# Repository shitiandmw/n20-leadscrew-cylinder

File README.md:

# n20-leadscrew-cylinder

**A 3D-printable linear actuator for a model excavator that looks like a hydraulic cylinder.** It is driven by a standard N20 gearmotor with an integrated M3 leadscrew, used exactly as bought.

The [Sand / Lab application](excavator_app/README.md) turns the existing ARM60 / Track R4 model into a Docker-deployable digging sandbox. A desktop displays the complete CAD assembly and a live sand pit: a deformable sand bed that slumps to its angle of repose, plus free grains wherever sand is cut, carried or poured; a phone pairs by QR code and controls the boom, stick, bucket, slew and tracks over WebSocket. It includes touch joysticks, keyboard controls, emergency stop, connection watchdogs, and verified scoop-and-pour physics. Run `docker compose up --build -d` from `excavator_app/` to start it.

The [complete tracked arm60 excavator](excavator_60mm/README.md) adds independent track drives, steel-pinned links, sprung idlers, bearing-supported geared slewing and a recessed slew cover around the existing 60 mm arm. Its R3 upper body follows the Cat 320 layout: cab front-left, tank housing and stepped toolbox front-right, an engine hood with a battery hatch, and a curved counterweight on the 189 mm tail-swing radius holding steel ballast. Two 18650 cells sit in a cradle sized from manufacturer datasheets. Track R4 adds Berco-referenced sprockets engaging steel bushings, rollers with two outer guide flanges, and a 394 mm track stance around the 308 mm upper platform. Offline playback shows the loaded contact simulation, including passive wheel rotation, idler take-up, forward/reverse travel and braking. The preview allows independent boom and slew travel; track clearance is managed by the operator. Its folder includes parametric CAD, printable parts, a complete STEP assembly, an offline preview, mechanical assembly instructions and reproducible geometry, load and physics simulations. Physical fit, powered operation and payload still require prototype testing.

The [R10 arm with two boom actuators and a deeper boomerang profile](excavator_arm_dual/README.md) implements the user's latest revision: symmetric boom drives at Y = ±50 mm and a hollow, tapered boom with a 76.7 mm middle section, retaining the original joint coordinates and five replaceable teeth. All four actuators are modeled independently. Fixed-base rigid-body simulations track both unloaded and 150 g cycles under an assumed 100 N limit per drive; each boom drive peaks at 58.4 N with the example load. CAD, printable parts, assembly instructions, an offline viewer and a 54-second motion video are included. A feedback-offset case demonstrates unequal load sharing; hardware synchronization, structural strength and soil interaction remain unverified.

R6–R9 and their motion-review files have been removed from the workspace at the user's request. The current arm is R10 in `excavator_arm_dual/`, with actuator dependencies in `actuator_v6/`. Earlier tracked designs remain in Git history. The complete vehicle and sandbox still use the earlier ARM60 model; R10 has not been integrated into them.

The new [ground-mounted excavator arm](excavator_arm/README.md) follows Cat 320 proportions at 1:12, with a 475 mm bent box boom, 241.7 mm stick and inward-facing bucket. Four V6 actuators use 100/120/75 mm leadscrews with regenerated matching parts and end-stop boards. It includes an [offline motion preview](excavator_arm/3D_preview.html), [STEP assembly](excavator_arm/step/excavator_arm_assembly.step), STL meshes, manufacturer references, dimensioned drawings and geometric validation. There is no vehicle chassis.

A separate [60 mm stroke edition](excavator_arm_60mm/README.md) uses four identical actuators and smaller 1:15 proportions: 380 mm boom, 193.3 mm stick and 80 mm bucket. Its [offline preview](excavator_arm_60mm/3D_preview.html), CAD and drawings are kept in their own folder; the 1:12 version remains available. Its actuator, V6-U60, is one of the three lengths (V6-S, V6-U60, V6-L) of the general-purpose [two-wire V6 actuator](actuator_v6/README.md). The current R4 model integrates the upper lift mounts into broad supports on the boom, with thicker cheeks and a shared steel cross-pin.

The motor's own leadscrew drives a brass nut inside the rod. Two Hall-effect end stops hide in a covered channel along the barrel. A small controller blocks each direction in hardware once that end is reached.

The geometry, STL/STEP files, wire routes, schematic and a self-contained 3D preview are all generated from parametric Python (CadQuery).

> **Status:** the design is complete and checked in CAD, but it has not been printed or powered yet. See [Status](#status).

## Features

- **Unmodified N20 leadscrew motor.** There is no coupler, bearing or separate screw. The brass M3 nut in the rod's carrier rides directly on the motor's screw. The gearbox seats on a step in the barrel and the rear cap backs the motor can.
- **Hydraulic-cylinder look:**
  - a round Ø21 mm yellow barrel;
  - Ø23 mm graphite end caps, with a wiper lip at the rod end;
  - a Ø9 mm chrome-look rod;
  - Ø14 mm clevis eyes for Ø3 mm pins;
  - a hose-style cable port with a TPU boot.
- **Hidden end stops.** Two DRV5033AJ Hall sensors sit in a dovetail channel under a flush cover strip, along with their resistors, capacitors and wiring. Each sensor slides ±3 mm for calibration.
- **Hardware direction gating.** A 74HC08 blocks motion toward an end as soon as that end's sensor trips, regardless of the firmware. The Arduino adds a current trip (ACS712), a 30 s run timeout and latching faults.
- **Parametric.** Change the leadscrew length and the stroke, barrel, rod, sensor positions, cover strip and wire routes all follow.
- **Self-checking outputs.**
  - The CAD build checks for interference over the full stroke, checks that every wire lands on its terminal, and checks that every STL is watertight.
  - The schematic generator rebuilds the connections from the drawing itself. It compares them with the netlist and with the firmware's pin constants.

## Specifications

Default build, for a 40 mm leadscrew:

| | |
|---|---|
| Stroke | 30 mm, plus 2 / 3 mm mechanical over-travel at retract / extend |
| Pin centres | 108 mm retracted → 138 mm extended |
| Barrel | Ø21 × 76 mm, end caps Ø23 mm |
| Rod | Ø9 mm |
| Clevis eyes | Ø14 mm, 10.4 mm thick, Ø3.2 mm holes |
| Motor | N20 gearmotor (10 × 12 mm body) with integrated M3 × 0.5 leadscrew |
| End stops | 2 × TI DRV5033AJQLPG and an N35 Ø4 × 2 mm magnet |
| Electronics | 6 V motor supply, 5 V logic: DRV8833, ACS712-05B, SN74HC08, Arduino Nano |

A longer screw gives a longer stroke. For example, a 60 mm screw gives 50 mm of stroke and 128 → 178 mm pin centres. See the [full table](actuator_v5/README.md#rebuild).

## A look inside

The left image is a section on the pin plane, showing the motor, leadscrew, brass nut in the rod's carrier, and magnet. The right image shows the sensor channel with the cover strip removed.

For an interactive view, download [`actuator_v5/3D_preview.html`](actuator_v5/3D_preview.html) and open it in any browser. It is a single 7 MB file that works offline; GitHub can't run it in the page. The preview includes:

- exterior, section, wiring and core-part views;
- a stroke slider;
- a live demo of the end stops and the overcurrent trip.

## Electronics

| Sheet 1: inside the actuator | Sheet 2: controller board |
|---|---|
|  |  |

- Full schematic: [`schematic.pdf`](actuator_v5/electronics/schematic.pdf) (A3).
- Harness, pin tables and commissioning: [`wiring.md`](actuator_v5/electronics/wiring.md).
- Firmware: [`actuator_protection.ino`](actuator_v5/electronics/actuator_protection/actuator_protection.ino).

## Repository layout

```
actuator_v5/
├── README.md           build guide: print settings, assembly order, calibration, rebuild
├── BOM.md              everything to buy, with reference designators
├── 3D_preview.html     offline interactive 3D viewer
├── stl/                printable parts (PETG); soft/ = TPU boot; fit_samples/ = test slices
├── step/               single parts plus the full assembly with wiring
├── electronics/        schematic, netlist, wiring.md, Arduino sketch, logic tests
├── images/             renders and analysis plots
├── references/         motor drawing and photo the design is based on
├── parameters.json     key dimensions of the current build
├── validation.json     geometric check report
└── source/             generators (CadQuery, schemdraw, Blender, three.js viewer)
```

## Building one

1. **Measure your leadscrew** from the gearbox front face to the tip. If it is not 40 mm, rebuild with `--screw-length` (see below).
2. **Print** the parts in `actuator_v5/stl/` in PETG and the boot in `stl/soft/` in TPU 95A. Print the four fit samples first.
3. **Buy** the parts in [`BOM.md`](actuator_v5/BOM.md).
4. **Assemble, wire and calibrate** by following the [build guide](actuator_v5/README.md#assembly-order). Check the motor direction first. Then set each Hall sensor so that it stops the motor just before the mechanical stop.

## Rebuilding from source

Tested with Python 3.11 and the packages in [`requirements.txt`](actuator_v5/source/requirements.txt) (CadQuery 2.8, trimesh, schemdraw, matplotlib, ReportLab, PyMuPDF). The renders need Blender 4.2.

```sh
cd actuator_v5
pip install -r source/requirements.txt
python source/build_v5.py --screw-length 40         # STEP/STL, meshes, validation (about 3 minutes)
python source/magnet_trigger.py                     # magnet model and Hall placement
python source/build_schematic.py                    # schematic, plus connectivity and firmware checks
python source/build_viewer.py                       # 3D_preview.html
blender -b -P source/render_v5.py -- --out images   # optional renders
```

`build_v5.py` stops with an error if any geometric check fails.

The logic tests need no hardware (run them from `actuator_v5/` too):

```sh
python electronics/check_direction_gates.py         # 74HC08 gates: all 16 input states
c++ -std=c++17 -UNDEBUG electronics/protection_logic_test.cpp -o /tmp/protection_test && /tmp/protection_test
```

## Status

Checked:

- **CAD** (results in [`validation.json`](actuator_v5/validation.json)):
  - no interference between parts, hardware and wires anywhere in the stroke;
  - all eight wires land on their terminals;
  - wire routes still clear with each sensor moved ±3 mm;
  - every STL is watertight.
- **Electronics:**
  - the schematic's connections match the netlist and the firmware's pin map;
  - the 74HC08 truth table passes;
  - the protection-logic unit test passes;
  - the Arduino sketch compiles against a stub of the Arduino API.

Not verified yet:

- printing and fit;
- the real motor's ratings, the gearbox's axial load capacity and PETG creep under load;
- magnetic switching on real parts (the magnet model ignores the steel screw and nut);
- the firmware running on a board.

The current trip (550 mA for 150 ms) is a starting value. Set it against the real motor during commissioning.

To do:

- the remaining renders (stroke positions and close-ups);
- an illustrated assembly guide PDF.

## License

No license has been chosen yet. The bundled three.js is MIT-licensed (see [`THREE_LICENSE.txt`](actuator_v5/source/vendor/THREE_LICENSE.txt)).

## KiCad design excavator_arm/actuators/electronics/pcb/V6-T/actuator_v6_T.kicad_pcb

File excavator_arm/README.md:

# Cat 320 reference arm with V6 leadscrew actuators — revision 2

A **1:12 reference-based model of the Cat 320 reach-boom excavator arm**, mounted on a fixed base with no chassis. The boom is a bent hollow box section, the stick has a compact pivot fork, and the bucket opens toward the machine. Two outside cylinders lift the boom; one cylinder drives the stick and one drives the bucket four-bar.

The V6 actuator architecture is retained, with **separate leadscrew lengths** for the three functions. Matching barrels, rods, end-stop PCBs and internal geometry are regenerated. This replaces the earlier straight plate-link arm; do not mix its structural files with this revision.

Open `3D_preview.html` directly in a browser. It works offline. `step/excavator_arm_assembly.step` is the editable assembly in the reference working pose. The guide, dimension drawing and validation reports are included alongside it.

## Real-machine basis

The manufacturer's Cat 320 technical specifications give the following dimensions. The model preserves all four exactly at 1:12.

| Dimension | Cat 320 reference | This model |
|---|---:|---:|
| Reach boom pin centres | 5700 mm | 475.000 mm |
| R2.9 stick pin centres | 2900 mm | 241.667 mm |
| 1.19 m³ HD pin-on bucket width | 1200 mm | 100.000 mm |
| Bucket tip radius | 1570 mm | 130.833 mm |

Sources: [Finning's Cat 320 product page](https://www.finning.com/en_GB/products/new/equipment/excavators/medium-excavators/126532.html) and [Caterpillar technical specifications](https://s7d2.scene7.com/is/content/Caterpillar/CM20240927-d80d6-c6a9b), pages 4, 5 and 11. Copies and source notes are under `references/`. Manufacturer side views were used to establish the bent boom profile, short stick, twin lift cylinders, pivot arrangement and inward bucket opening.

**This is an adapted model, not factory CAD.** The four dimensions above are published values. Detailed section outlines, pin locations, clevis widths and ground bracket are engineering adaptations estimated from the imagery and fitted to the V6 actuators. The factory cylinder dimensions, complete working envelope and load ratings are not claimed for this model. The fixed base replaces only the original arm-support structure; no vehicle chassis, cab or turret is modeled.

## Resized actuators

| Function | Variant | Quantity | Screw length | Nominal stroke | Pin spacing, closed → open |
|---|---|---:|---:|---:|---:|
| Paired boom lift | V6-B | 2 | 100 mm | 85 mm | 165 → 250 mm |
| Stick crowd | V6-T | 1 | 120 mm | 105 mm | 185 → 290 mm |
| Bucket curl | V6-K | 1 | 75 mm | 60 mm | 140 → 200 mm |

Screw lengths are measured from the gearbox front face to the tip. The V6 relationship is **closed pin spacing = screw length + 65 mm**, and **stroke = screw length − 15 mm**. Keep the stock right-hand M3 × 0.5 thread, Ø8 rod, 16.10 × 14.70 housing section, 6 mm-thick eyes and Ø3.2 eye holes for Ø3 pins. Each end retains 3 mm of mechanical reserve beyond nominal travel. Do not command that reserve.

`actuators/` contains the three matched sets, their individual STEP/STL parts, assembled actuator STEP files, new board Gerbers/KiCad/BOM/placement files, parameters and verification. Print or order two B sets, one T and one K. Select or modify the motor's integrated screw to the specified length; the original 55 mm V6-S screw is not the correct part for these three new sizes. The motor body, gearbox mounting and anti-rotation carrier follow the original V6 design.

The original V6 files in sibling `actuator_v6/` remain unchanged and are source dependencies. Do not substitute an original V6-S PCB into a longer actuator. Its Hall positions and board length would be wrong.

## Coordinates and transmission

Global X points from the base toward the work area, Z is upward and all hinge axes are parallel to Y. Positive angles turn +X toward +Z. Boom coordinates originate at O, stick coordinates at E, and bucket coordinates at H.

| Point | Local frame | X | Z | Purpose |
|---|---|---:|---:|---|
| O | Ground | 0 | 110 | Boom hinge |
| A | Ground | 70 | 75 | Both boom actuator rear eyes |
| B | Boom | 190 | 75 | Both boom actuator rod eyes |
| E | Boom | 475 | 0 | Stick hinge |
| C | Boom | 263 | 116 | Stick actuator rear eye |
| D | Stick | −62 | 14 | Stick actuator rod eye |
| F | Stick | 35 | 36 | Bucket actuator rear eye |
| J | Stick | 192 | 16 | Rocker hinge |
| H | Stick | 241.667 | 0 | Bucket hinge |
| R | Rocker, origin J | 52 | 0 | Bucket rod eye and coupler pin |
| Q | Bucket | 32.889 | −11.971 | Coupler pin |
| T | Bucket | −104 | −79.381 | Cutting-tip reference |

Boom cylinders are at Y = −42 and +42; their pin-to-pin lengths are identical at every pose. The other cylinders are centred at Y = 0. The four-bar lengths are J–R = 52, R–Q = 65 and H–Q = 35 mm. The fixed J–H link is 52.180 mm. Assemble the illustrated branch; the other circle-intersection branch is not the intended digging mechanism.

**Electrical A+ / B− extends:** the boom rises, the stick moves inward and the bucket cutting lip curls upward toward the machine. Reverse polarity reverses these actions. Electrical terminal names A/B are separate from the mechanical point labels.

A right-hand M3 × 0.5 screw makes **2 revolutions per millimetre**. With the screw held axially and the nut prevented from turning, clockwise rotation **viewed from the rod end toward the motor** extends the rod. Local screw angle is −2π·stroke/0.5 with +Z toward the rod. Full nominal strokes require 170 / 210 / 120 revolutions for boom / stick / bucket. The original screw mesh uses pitch rings rather than a helical manufacturing thread; the viewer applies the correct rotation relationship and adds a rotation witness.

Nominal joint ranges are approximately 1.72–69.17° boom elevation, −39.26 to −150.80° stick relative to boom, and 131.11 to 12.86° bucket relative to stick. The bucket body's zero orientation has its mouth and teeth toward −X. The reference pose has boom 31°, stick −114° relative to boom and the cutting lip just above Z = 0.

Use three reversible 6 V control functions, with the two boom units coordinated as one mechanical axis. They must never be commanded to unequal lengths. Match their physical end stops before powered operation; the V6 has no external position-feedback output. The viewer's exact position sliders are geometric controls, not a supplied hardware position controller.

## Mounts, parts and assembly

The fixed plate is **165 × 164 × 12 mm**, X = −55 to +110, Y = ±82. Four Ø6.6 holes at (X,Y) = (−40,±65), (95,±65) accept M6 fixing bolts. The boom root is 110 mm above the mounting plane. The compact root support uses paired bearing cheeks and gussets; boom lift cylinders have their own lower clevises.

Main pivots O, E and H use **Ø6 steel shafts in Ø6.2 holes**. Cylinder and linkage pivots use **Ø3 shafts in Ø3.2 holes**. The boom box is 48 mm wide, the stick 32 mm wide, and the bucket 100 mm wide. Nominal box walls are 4 mm. The distal boom fork is open over its last 70 mm to clear the stick through its full range. Its bearing cheeks remain on either side of the stick.

There are eight structural STL files: fixed base, boom, stick, two rockers, two couplers and bucket. These are model meshes with valid closed solids. **The 509 mm-long monolithic boom needs a large printer or a separately engineered split/joint before manufacture**; do not mistake a watertight STL for a ready-to-load printed assembly. Individual structural STEP files preserve assembly coordinates. STLs are laid onto Z = 0 for slicing. The hollow boxes have trapped internal cavities; review the intended printing process and supports before fabrication.

| Shaft | Quantity | Location |
|---|---:|---|
| Ø6 × 82 | 1 | O |
| Ø6 × 60 | 2 | E,H |
| Ø3 × 36 | 6 | A-left/right, B-left/right, C,F |
| Ø3 × 42 | 1 | D |
| Ø3 × 58 | 1 | J |
| Ø3 × 70 | 2 | R,Q |

Use two collars per shaft: six Ø6-bore collars with nominal Ø11 × 4 envelopes and twenty Ø3-bore collars with nominal Ø7 × 3 envelopes. Set screws are omitted from the model. Collars have 0.3 mm running clearance to the outer faces. Confirm the actual bought collars fit those envelopes.

| Spacer, OD × ID × length | Quantity | Location |
|---|---:|---|
| 9 × 6.2 × 2.8 | 2 | O |
| 9 × 6.2 × 1.8 | 4 | E,H |
| 7 × 3.2 × 4.8 | 12 | Both sides of the six eyes at A-left/right, B-left/right, C,F |
| 7 × 3.2 × 6.8 | 2 | D |
| 7 × 3.2 × 1.8 | 2 | J |
| 7 × 3.2 × 14.8 | 2 | R, actuator eye to rockers |
| 7 × 3.2 × 0.8 | 4 | R,Q, rockers/horns to outer couplers |

1. Anchor the fixed base to a rigid surface using four M6 bolts and suitable washers/nuts. Keep the pivot shafts horizontal and parallel.
2. Fit the boom at O, the stick at E and the bucket at H with the listed spacers and collars.
3. Fit paired rockers on J in Y bands 18–24 and −24 to −18. Fit outer couplers at R and Q in bands 25–30 and −30 to −25. The bucket mouth must face the base in the reference pose.
4. Assemble and calibrate the four matching V6 actuators. Fit the B pair at A–B, T at C–D and K at F–R, using the eye spacers. Keep the two B strokes equal.
5. Route flexible two-core cables with service loops at the moving pivots. External cable loops are not routed or collision-checked by this model.
6. Jog unloaded at low speed, check all three motion directions and verify actual end-stop reversal. Calibrate the paired boom endpoints together before combined motion.

The working envelope includes positions below Z = 0, just as a real excavator digs below its support surface. The viewer shows the mounting plane and leaves the working area visible. On a solid-floor demonstration rig, restrict those positions or mount beside a clear recess/bench edge. Do not sweep the model through a solid floor.

## Validation and limitations

`validation.json` records reference dimensional ratios, 461 transmission samples, actuator/link closure, inward bucket orientation, upward lip motion during curl, and exact-solid interference checks at **134 combined configurations**: 125 nominal grid points, eight mechanical-reserve corners and the reference pose. It also samples the tooth envelope at 9,261 configurations. Sampling is not a proof of continuous collision freedom.

`actuators/validation.json` records fresh internal CAD and STL checks for B, T and K. `actuators/electronics/pcb/validation.json` records board design-rule checks and independent Gerber readback. All three regenerated boards have zero DRC errors and zero readback mismatch. Electronics topology and magnetic sensing assumptions are inherited from V6; this is not a new powered hardware or thermal test.

`source/export_report.json` records structural single-solid, watertight STL and STEP import checks. `browser_validation.json` records independent Python/JavaScript pin-position comparison, controls, offline rendering and mobile layout.

The published Cat dimensions do not transfer its forces or payload to this model. Motor gearbox axial capacity, long printed rods, joint deflection, print process, creep, real end stops, synchronized boom drive and external wiring require physical prototype testing. No payload rating is supplied.

## Rebuild

Keep `excavator_arm/` beside `actuator_v6/`. Use Python 3.11 and the packages in `source/requirements.txt`. CadQuery needs the appropriate system OpenGL libraries. Node/Playwright with Chromium is needed only for the viewer checks.

```sh
python excavator_arm/source/build_actuators.py
python excavator_arm/source/build_arm.py
python excavator_arm/source/validate_arm.py
python excavator_arm/source/build_viewer.py
python excavator_arm/source/build_guide.py
python excavator_arm/source/package_delivery.py
```

`source/kinematics.py` is the single dimensional reference and supplies the viewer configuration. Original V6 source files are imported read-only; board caches and generated files are redirected into `actuators/`. The package carries the bundled three.js MIT license and identifies manufacturer reference images separately.

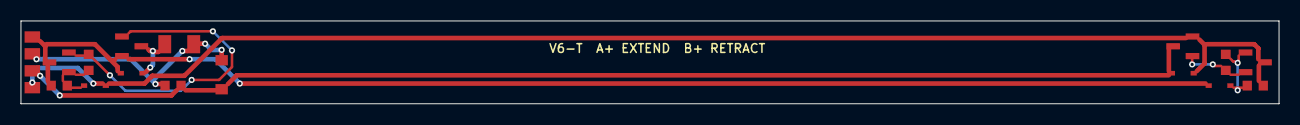
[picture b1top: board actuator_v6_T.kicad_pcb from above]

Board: 2 copper layers, 121.6 x 8.0 mm, 19 parts (0 on the bottom side), 9 nets.

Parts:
C1, C2: 1 µF 50 V X5R; C_0603_1608Metric
C3: 100 nF 50 V X7R; C_0603_1608Metric
D1, D2: 1N4148WS; D_SOD-323
D3: SMF7.0CA; D_SOD-123F
D4, D5: B5819WS; D_SOD-323
F1: 0.12 A PPTC; Fuse_1206_3216Metric
J_A: cable wire A (+ = extend); WirePad_1.1x1.5
J_B: cable wire B (+ = retract); WirePad_1.1x1.5
J_M+: to motor terminal +; WirePad_1.1x1.5
J_M-: to motor terminal -; WirePad_1.1x1.5
Q1, Q2: AO3400A; SOT-23
R1, R2: 1 MΩ 1 %; R_0603_1608Metric
U1, U2: DRV5033AJQDBZR; SOT-23

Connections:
A: C1.2, D2.2, D4.2, J_A.1, Q1.2, U1.3
A_SW: D4.1, F1.1, Q1.3
B: C2.2, D1.2, D5.2, J_B.1, Q2.2, U2.3
G_EXT: Q2.1, R2.2, U2.2
G_RET: Q1.1, R1.2, U1.2
MOT+: C3.1, D3.1, F1.2, J_M+.1
MOT-: C3.2, D3.2, D5.1, J_M-.1, Q2.3
VCC_EXT: C2.1, D2.1, R2.1, U2.1
VCC_RET: C1.1, D1.1, R1.1, U1.1
